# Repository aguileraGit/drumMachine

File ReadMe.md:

- Downloaded SVG: https://www.flaticon.com/free-icon/drum-set_1776571
- Used Inkspace to slice and dice into layers (See folder)
- Convert SVG layers into Eagle scr. (See folder) https://gfwilliams.github.io/svgtoeagle/
 - Mask: Take part to mask. Add 10px stroke. Select Path. Path-Outset
- Merge into ItsyBitsy-M0: https://github.com/adafruit/Adafruit-ItsyBitsy-M0-PCB
- LEDs: https://www.digikey.com/products/en?mpart=3341&v=1528
- https://learn.adafruit.com/introducing-itsy-bitsy-m0/pinouts
- Touch Pins: The following pins have hardware capacitive touch capability: A0, A1, A2, A3, A4, A5, and D9

- ~~Need to add D13 back in!~~
- ~~Is AREF needed?~~ Deleted
- ~~Need to reverse component side~~ None to be found
- ~~SWDIO and SWCLK header - 4 pin square~~

207 - Title - Silkscreen
206 - Bass Drum - Top Copper
205 - Top Drums - Top Copper & Soldermask
204 - Drums & Cymbals - Top Copper
203 - Silkscreen

Waterproof USB Micro: https://www.digikey.com/short/zphm51

Reset pull-up?

Memory:
- https://www.digikey.com/short/zp9vq1

USB:
- Adafruit: https://www.adafruit.com/product/4023
- A108263CT-ND
- 3D Model: https://www.te.com/usa-en/product-2040002-1.html?te_bu=Dat&te_type=other&te_campaign=eda_usa_sg-snap-3d&elqCampaignId=20145#pdp-documents-tab

LED:
- https://www.digikey.com/short/zphmfp

uC:
- https://www.digikey.com/short/zphmwt

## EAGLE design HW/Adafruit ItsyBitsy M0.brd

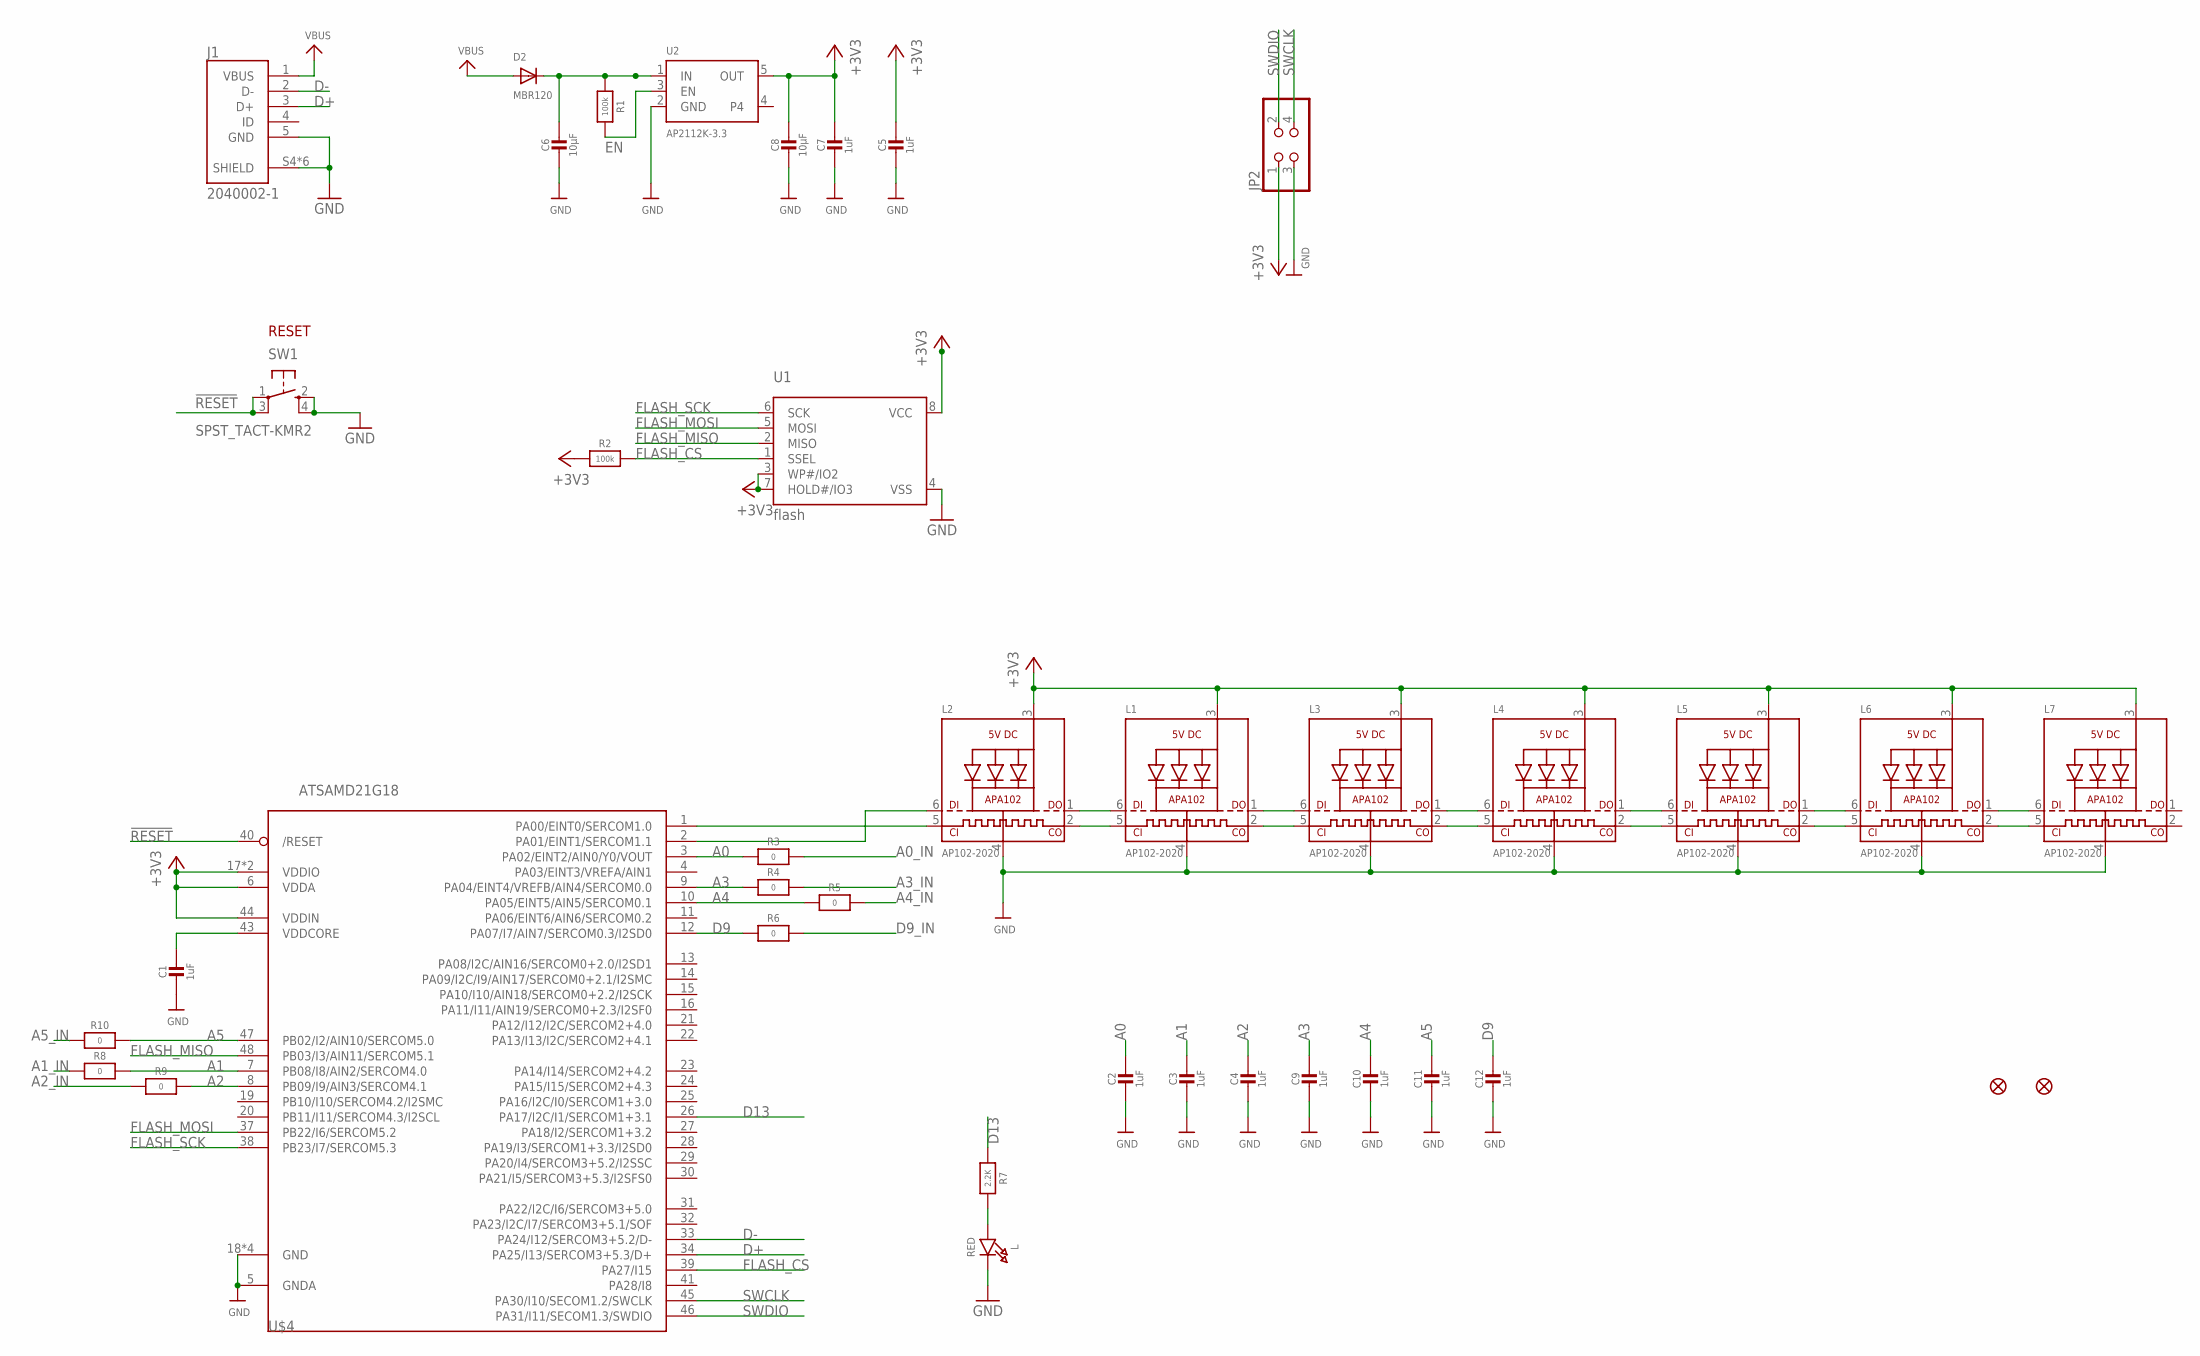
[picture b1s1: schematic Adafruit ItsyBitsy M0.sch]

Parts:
C1, C5, C7: 1uF; 0603-NO; JLC_PN 1uF
C2, C3, C4, C9, C10, C11, C12: 1uF; 0603-NO
C6, C8: 10µF; 0805-NO; JLC_PN 10uF
D2: MBR120; SOD-123FL; JLC_PN MBR120LSF
J1: 2040002-1; TE_2040002-1
JP2: PINHD-2X2; 2X02
L: RED; CHIPLED_0805_NOOUTLINE; JLC_PN RED LED
L1, L2, L3, L4, L5, L6, L7: AP102-2020; APA102_2020
R1, R2: 100k; 0603-NO; JLC_PN 100k
R3, R4, R5, R6, R8, R9, R10: 0; 0603-NO; JLC_PN 0
R7: 2.2K; 0603-NO; JLC_PN 2.2k
SW1: SPST_TACT-KMR2; KMR2
U1: flash; USON8
U2: AP2112K-3.3; SOT23-5; JLC_PN AP2112K-3.3TRG1
U$4: ATSAMD21G18; TQFN48_7MM
U$34, U$35: FIDUCIAL_1MM

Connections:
!RESET: SW1.1, SW1.3 (P1), U$4.40 (/RESET)
+3V3: C5.1, C7.1, C8.1, JP2.1, L1.3 (VDD), L2.3 (VDD), L3.3 (VDD), L4.3 (VDD), L5.3 (VDD), L6.3 (VDD), L7.3 (VDD), R2.1, U1.3 (WP#/IO2), U1.7 (HOLD#/IO3), U1.8 (VCC), U2.5 (OUT), U$4.6 (VDDA), U$4.17 (VDDIO), U$4.36 (VDDIO), U$4.44 (VDDIN)
A0: C2.1, R3.1, U$4.3 (PA02/EINT2/AIN0/Y0/VOUT)
A0_IN: R3.2
A1: C3.1, R8.2, U$4.7 (PB08/I8/AIN2/SERCOM4.0)
A1_IN: R8.1
A2: C4.1, R9.2, U$4.8 (PB09/I9/AIN3/SERCOM4.1)
A2_IN: R9.1
A3: C9.1, R4.1, U$4.9 (PA04/EINT4/VREFB/AIN4/SERCOM0.0)
A3_IN: R4.2
A4: C10.1, R5.1, U$4.10 (PA05/EINT5/AIN5/SERCOM0.1)
A4_IN: R5.2
A5: C11.1, R10.2, U$4.47 (PB02/I2/AIN10/SERCOM5.0)
A5_IN: R10.1
D9: C12.1, R6.1, U$4.12 (PA07/I7/AIN7/SERCOM0.3/I2SD0)
D9_IN: R6.2
D13: R7.1, U$4.26 (PA17/I2C/I1/SERCOM1+3.1)
D+: J1.3 (D+), U$4.34 (PA25/I13/SERCOM3+5.3/D+)
D-: J1.2 (D-), U$4.33 (PA24/I12/SERCOM3+5.2/D-)
EN: R1.2, U2.3 (EN)
FLASH_CS: R2.2, U1.1 (SSEL), U$4.39 (PA27/I15)
FLASH_MISO: U1.2 (MISO), U$4.48 (PB03/I3/AIN11/SERCOM5.1)
FLASH_MOSI: U1.5 (MOSI), U$4.37 (PB22/I6/SERCOM5.2)
FLASH_SCK: U1.6 (SCK), U$4.38 (PB23/I7/SERCOM5.3)
GND: C1.2, C2.2, C3.2, C4.2, C5.2, C6.2, C7.2, C8.2, C9.2, C10.2, C11.2, C12.2, J1.5 (GND), J1.S4 (SHIELD), J1.S5 (SHIELD), J1.SH1 (SHIELD), J1.SH2 (SHIELD), J1.SH3 (SHIELD), J1.SH4 (SHIELD), JP2.3, L.C, L1.4 (GND), L2.4 (GND), L3.4 (GND), L4.4 (GND), L5.4 (GND), L6.4 (GND), L7.4 (GND), SW1.2 (S), SW1.4 (S1), U1.4 (VSS), U2.2 (GND), U$4.5 (GNDA), U$4.18 (GND), U$4.35 (GND), U$4.42 (GND), U$4.THERMAL (GND)
unnamed: L2.5 (CKI), U$4.1 (PA00/EINT0/SERCOM1.0)
unnamed: L.A, R7.2
unnamed: L1.6 (DI), L2.1 (DO)
unnamed: L1.5 (CKI), L2.2 (CKO)
unnamed: L2.6 (DI), U$4.2 (PA01/EINT1/SERCOM1.1)
unnamed: L1.1 (DO), L3.6 (DI)
unnamed: L1.2 (CKO), L3.5 (CKI)
unnamed: L3.1 (DO), L4.6 (DI)
unnamed: L3.2 (CKO), L4.5 (CKI)
unnamed: L4.1 (DO), L5.6 (DI)
unnamed: L4.2 (CKO), L5.5 (CKI)
unnamed: L5.1 (DO), L6.6 (DI)
unnamed: L5.2 (CKO), L6.5 (CKI)
unnamed: L6.1 (DO), L7.6 (DI)
unnamed: L6.2 (CKO), L7.5 (CKI)
SWCLK: JP2.4, U$4.45 (PA30/I10/SECOM1.2/SWCLK)
SWDIO: JP2.2, U$4.46 (PA31/I11/SECOM1.3/SWDIO)
VBUS: D2.A, J1.1 (VBUS)
VDDCORE: C1.1, U$4.43 (VDDCORE)
VHI: C6.1, D2.C, R1.1, U2.1 (IN)

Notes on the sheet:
RESET

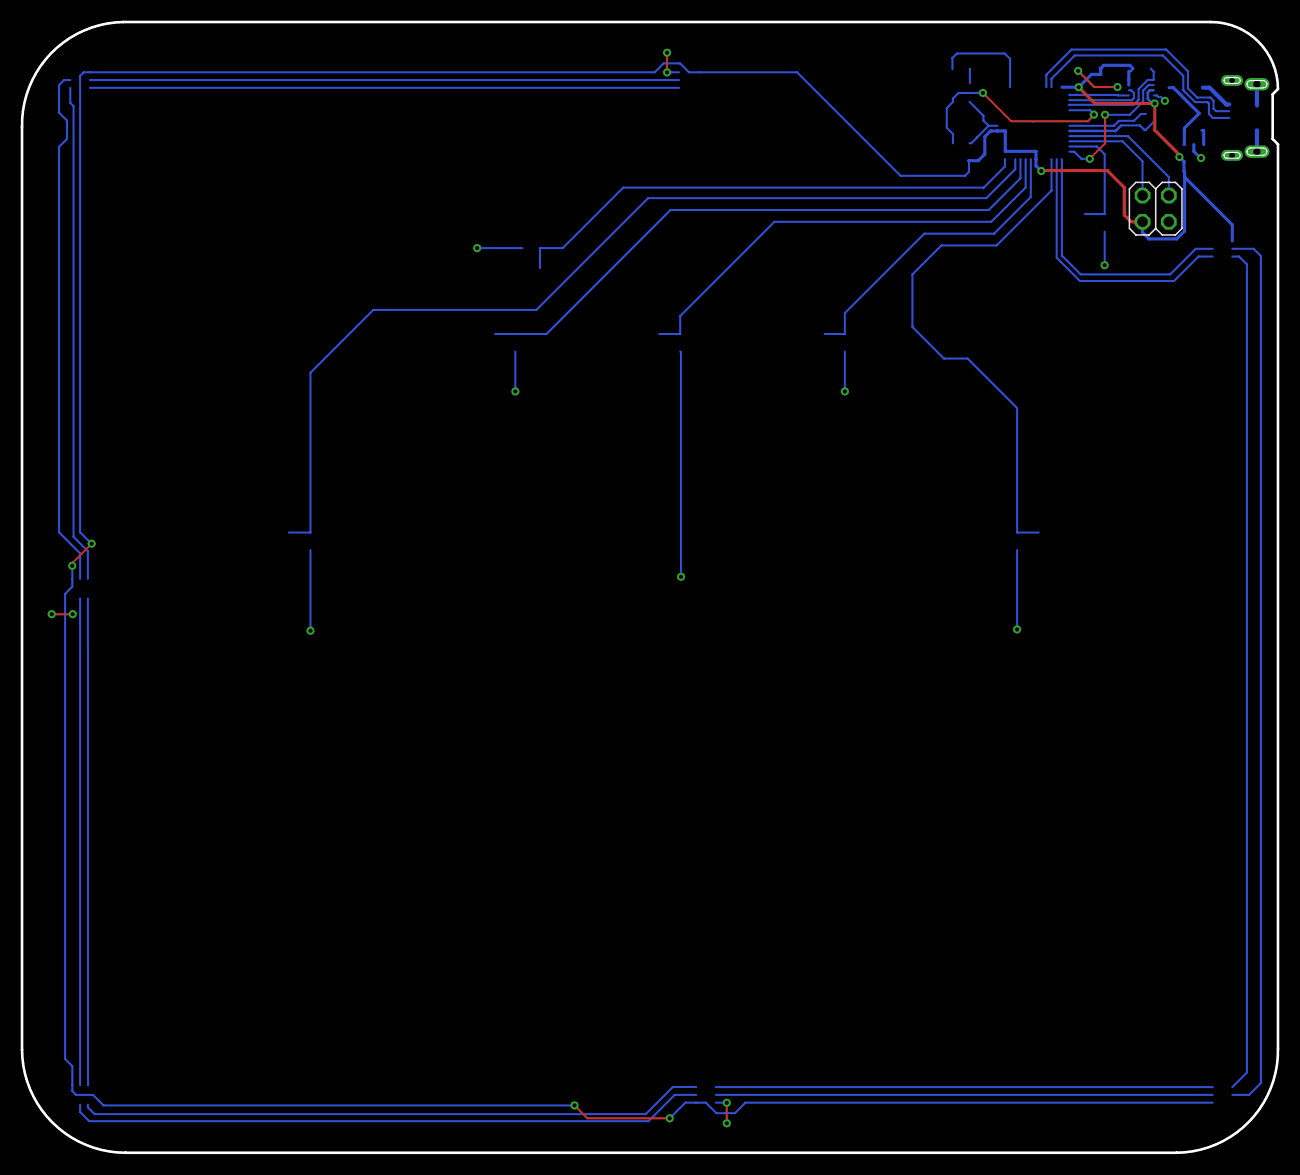
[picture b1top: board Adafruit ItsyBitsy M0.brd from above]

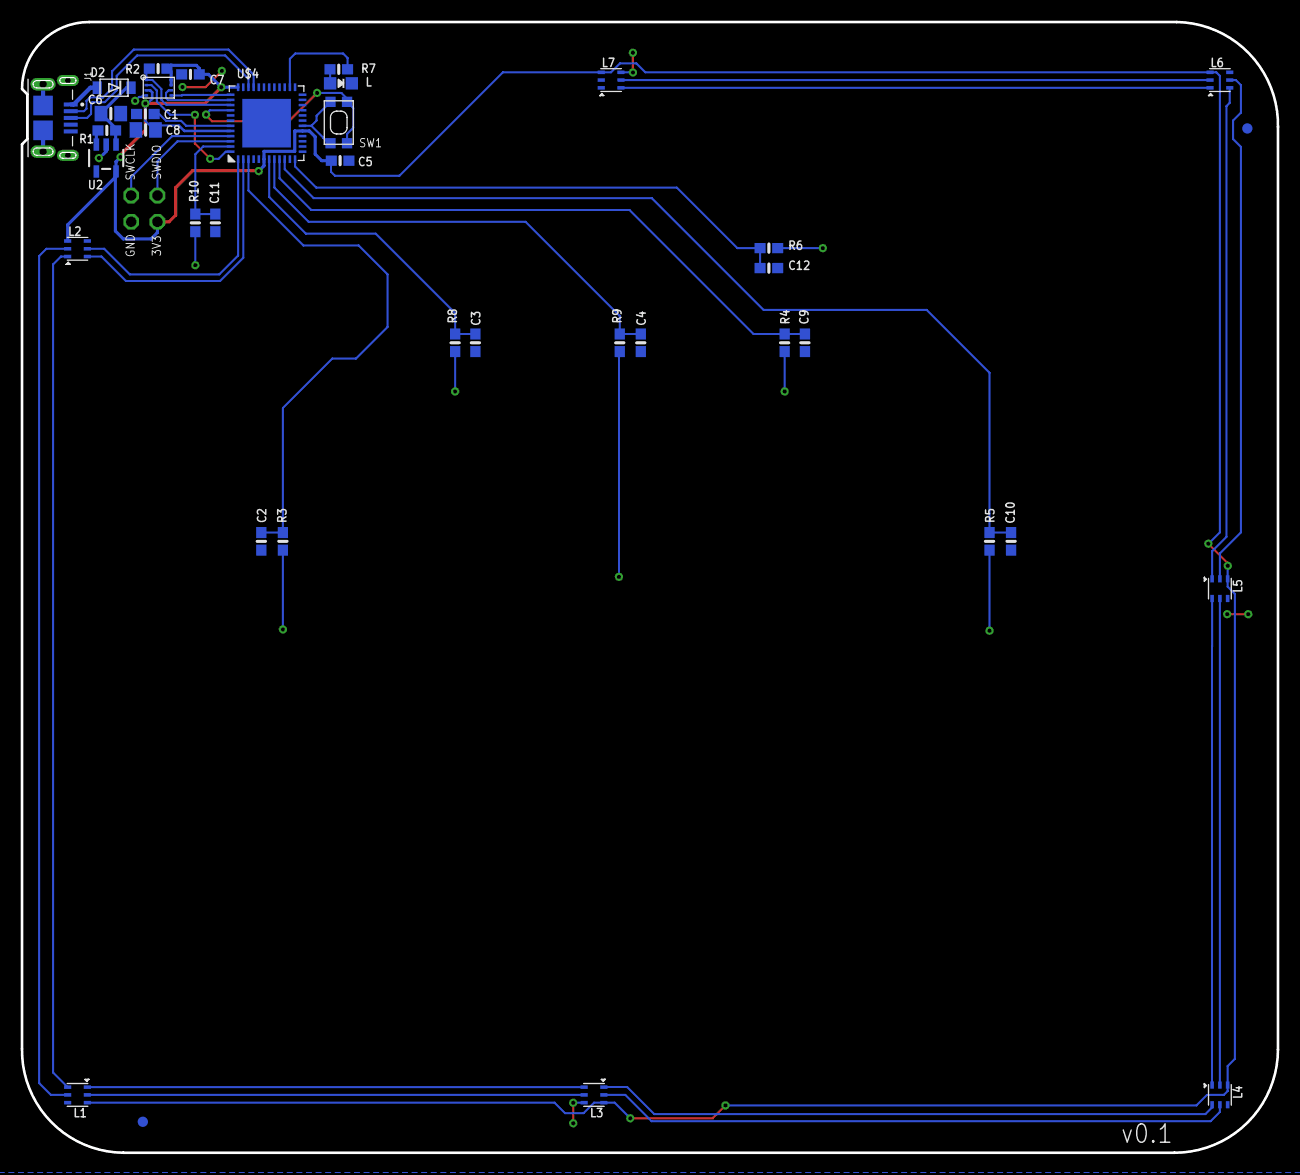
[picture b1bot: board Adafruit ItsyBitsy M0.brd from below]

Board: 2 copper layers, 121.3 x 109.2 mm, 41 parts (39 on the bottom side), 38 nets.

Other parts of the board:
U$14: ITSYM0_TOP
U$15: ITSYM0_BOT

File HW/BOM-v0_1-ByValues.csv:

"Qty";"Value";"Device";"Package";"Parts";"Description";"AVAILABILITY";"BOM";"CENTERLINE_PITCH";"COMMENT";"DESCRIPTION";"DK_PN";"JLC_PN";"MF";"MP";"NUMBER_OF_POSITIONS";"PACKAGE";"PN";"POPULARITY";"PRICE";"PRODUCT_TYPE";"TE_PURCHASE_URL";
"1";"";"PINHD-2X2";"2X02";"JP2";"PIN HEADER";"";"";"";"";"";"";"";"";"";"";"";"";"0";"";"";"";
"7";"0";"RESISTOR_0603_NOOUT";"0603-NO";"R3, R4, R5, R6, R8, R9, R10";"Resistors";"";"";"";"";"";"P0.0GCT-ND";"0";"";"";"";"";"";"";"";"";"";
"2";"100k";"RESISTOR_0603_NOOUT";"0603-NO";"R1, R2";"Resistors";"";"";"";"";"";"P100KDBCT-ND";"100k";"";"";"";"";"";"";"";"";"";
"2";"10µF";"CAP_CERAMIC0805-NOOUTLINE";"0805-NO";"C6, C8";"Ceramic Capacitors";"";"";"";"";"";"490-14381-1-ND";"10uF";"";"";"";"";"";"";"";"";"";
"3";"1uF";"CAP_CERAMIC0603_NO";"0603-NO";"C1, C5, C7";"Ceramic Capacitors";"";"";"";"";"";"399-17705-1-ND";"1uF";"";"";"";"";"";"";"";"";"";
"7";"1uF";"CAP_CERAMIC0603_NO";"0603-NO";"C2, C3, C4, C9, C10, C11, C12";"Ceramic Capacitors";"";"";"";"";"";"";"";"";"";"";"";"";"";"";"";"";
"1";"2.2K";"RESISTOR_0603_NOOUT";"0603-NO";"R7";"Resistors";"";"";"";"";"";"P2.2KDBCT-ND";"2.2k";"";"";"";"";"";"";"";"";"";
"1";"2040002-1";"2040002-1";"TE_2040002-1";"J1";"Conn USB Type B RCP 5 POS 0.65mm Solder RA SMD 5 Terminal 1 Port T/R";"Unavailable";"";".65 mm[.025 in]";"2040002-1";" Conn Micro USB 2.0 Type B RCP 5 POS 0.65mm Solder RA SMD 5 Terminal 1 Port T/R ";"A108263CT-ND";"";"TE Connectivity";"2040002-1";"5";"None";"2040002-1";"";"None";"Connector";"https://www.te.com/usa-en/product-2040002-1.html?te_bu=Cor&t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";
"7";"AP102-2020";"APA1022020";"APA102_2020";"L1, L2, L3, L4, L5, L6, L7";"APA102/DotStar Pixels";"";"";"";"";"";"1528-1826-ND";"";"";"";"";"";"3341";"";"";"";"";
"1";"AP2112K-3.3";"VREG_SOT23-5";"SOT23-5";"U2";"SOT23-5 Fixed Voltage Regulators";"";"";"";"";"";"AP2112K-3.3TRG1DICT-ND";"AP2112K-3.3TRG1";"";"";"";"";"AP2112K-3.3TRG1";"";"";"";"";
"1";"ATSAMD21G18";"ATSAMD21G_QFN";"TQFN48_7MM";"U$4";"";"";"";"";"";"";"ATSAMD21G18A-MU-ND";"";"";"";"";"";"ATSAMD21G18A-MU";"";"";"";"";
"2";"FIDUCIAL_1MM";"FIDUCIAL_1MM";"FIDUCIAL_1MM";"U$34, U$35";"Fiducial Alignment Points";"";"EXCLUDE";"";"";"";"";"";"";"";"";"";"";"";"";"";"";
"1";"MBR120";"DIODE_SOD-123FL";"SOD-123FL";"D2";"Diode";"";"";"";"";"";"MBR120LSFT1GOSCT-ND";"MBR120LSF";"";"";"";"";"";"";"";"";"";
"1";"RED";"LED0805_NOOUTLINE";"CHIPLED_0805_NOOUTLINE";"L";"LED";"";"";"";"";"";"475-1415-1-ND";"RED LED";"";"";"";"";"";"";"";"";"";
"1";"SPST_TACT-KMR2";"SPST_TACT-KMR2";"KMR2";"SW1";"SMT 6mm switch, EVQQ2 series";"";"";"";"";"";"401-1426-1-ND";"";"";"";"";"";"KMR211GLFS";"";"";"";"";
"1";"flash";"SPIFLASH_8PINUX";"USON8";"U1";"SOIC8 SPI Flash";"";"";"";"";"";"1092-1184-1-ND";"";"";"";"";"";"MX25R2035FZUIL0";"";"";"";"";

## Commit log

2020-06-04 Init Commit
2020-10-13 Adding FW, CAM, and BOM
2020-10-13 Adding PDF of schematics

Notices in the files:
parts and their libraries:
microbuilder: This work is placed in the public domain, and may be freely used for commercial and non-commercial work with the following conditions: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
